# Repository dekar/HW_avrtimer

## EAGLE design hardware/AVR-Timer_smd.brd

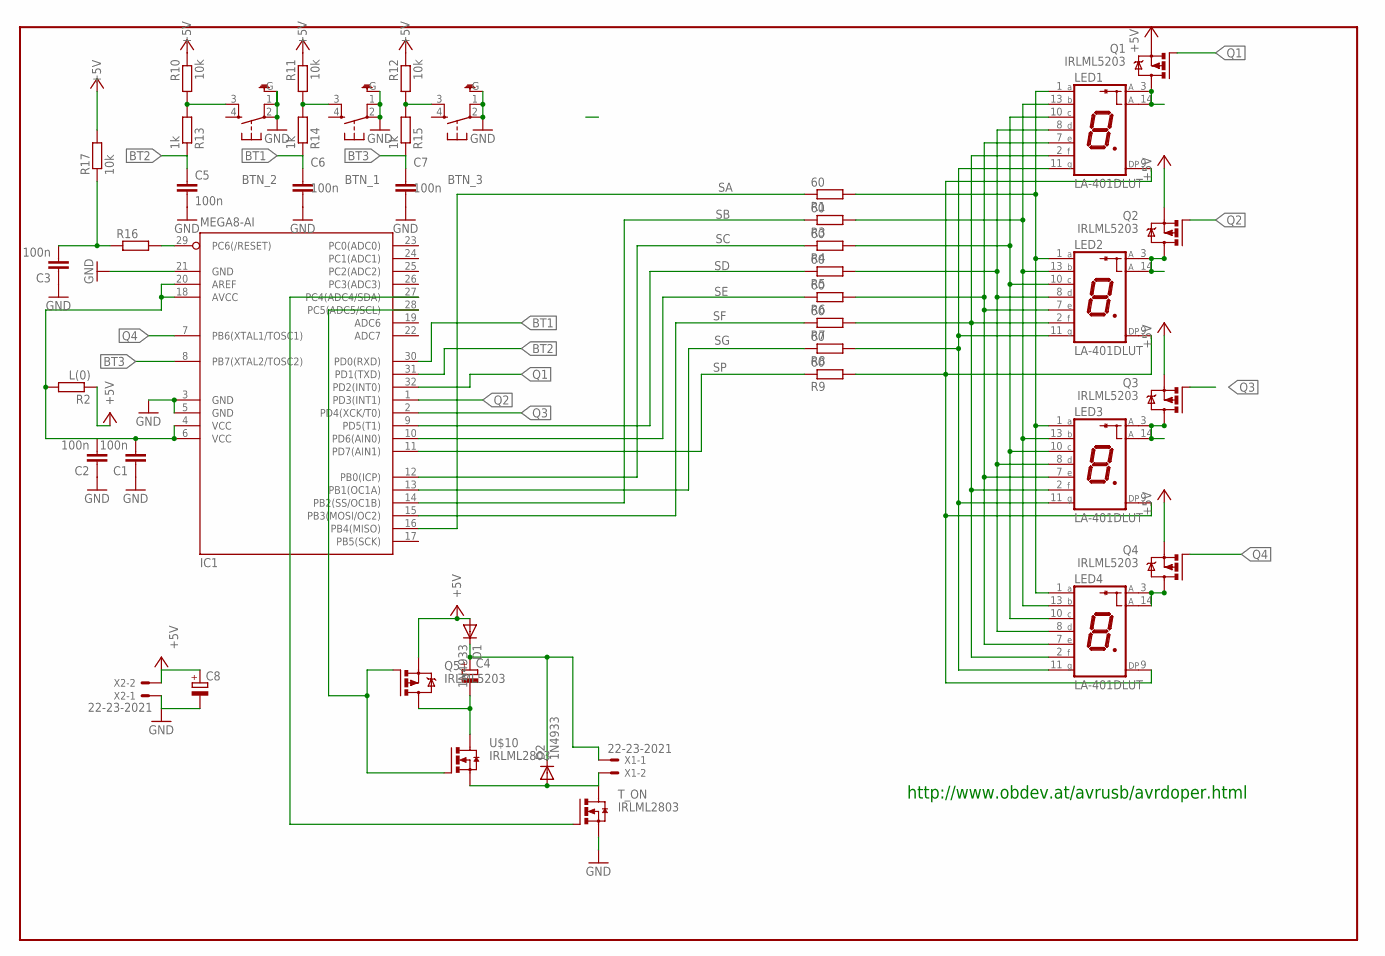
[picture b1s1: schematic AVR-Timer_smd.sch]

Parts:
BTN_1, BTN_2, BTN_3: 10-XXG; B3F-10XXG
C1, C2, C3, C5, C6, C7: 100n; C0805K
C4, C8: CPOL-EUE5-8.5; E5-8,5
D1, D2: 1N4933; DO41-10
IC1: MEGA8-AI; TQFP32-08
LED1, LED2, LED3, LED4: LA-401DLUT; MY_LUT
Q1, Q2, Q3, Q4, Q5: IRLML5203; MICRO3
R1, R3, R4, R5, R6, R7, R8, R9: 60; M0805
R2: L(0); M1206
R10, R11, R12: 10k; M0805
R13, R14, R15: 1k; M0805
R16: R-EU_M1206; M1206
R17: 10k; M1206
T_ON: IRLML2803; SUPER-SOT3
U$10: IRLML2803; SUPER-SOT3
X1: 22-23-2021
X2: 22-23-2021; MPN 22-23-2021

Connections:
+5V: C8.+, D1.A, Q1.2 (S), Q2.2 (S), Q3.2 (S), Q4.2 (S), Q5.2 (S), R2.1, R10.1, R11.1, R12.1, R17.2, X2.2
BT1: C6.1, IC1.30 (PD0(RXD)), R14.1
BT2: C5.1, IC1.31 (PD1(TXD)), R13.1
BT3: C7.1, IC1.8 (PB7(XTAL2/TOSC2)), R15.1
GND: BTN_1.1, BTN_1.2, BTN_1.G (GND), BTN_2.1, BTN_2.2, BTN_2.G (GND), BTN_3.1, BTN_3.2, BTN_3.G (GND), C1.1, C2.1, C3.1, C5.2, C6.2, C7.2, C8.-, IC1.3 (GND), IC1.5 (GND), IC1.21 (GND), T_ON.2 (S), X2.1
unnamed: C1.2, C2.2, IC1.4 (VCC), IC1.6 (VCC), IC1.18 (AVCC), IC1.20 (AREF), R2.2
unnamed: BTN_2.3 (S1), R10.2, R13.2
unnamed: BTN_1.3 (S1), R11.2, R14.2
unnamed: BTN_3.3 (S1), R12.2, R15.2
unnamed: C3.2, R16.1, R17.1
unnamed: LED1.1 (A), LED2.1 (A), LED3.1 (A), LED4.1 (A), R1.2
unnamed: LED1.13 (B), LED2.13 (B), LED3.13 (B), LED4.13 (B), R3.2
unnamed: LED1.10 (C), LED2.10 (C), LED3.10 (C), LED4.10 (C), R4.2
unnamed: LED1.8 (D), LED2.8 (D), LED3.8 (D), LED4.8 (D), R5.2
unnamed: LED1.7 (E), LED2.7 (E), LED3.7 (E), LED4.7 (E), R6.2
unnamed: LED1.9 (DP), LED2.9 (DP), LED3.9 (DP), LED4.9 (DP), R9.2
unnamed: LED1.11 (G), LED2.11 (G), LED3.11 (G), LED4.11 (G), R8.2
unnamed: LED3.3 (A), LED3.14 (A), Q3.3 (D)
unnamed: LED2.3 (A), LED2.14 (A), Q2.3 (D)
unnamed: LED4.3 (A), LED4.14 (A), Q4.3 (D)
unnamed: LED1.2 (F), LED2.2 (F), LED3.2 (F), LED4.2 (F), R7.2
unnamed: LED1.3 (A), LED1.14 (A), Q1.3 (D)
unnamed: C4.-, Q5.3 (D), U$10.3 (D)
unnamed: IC1.28 (PC5(ADC5/SCL)), Q5.1 (G), U$10.1 (G)
unnamed: D2.A, T_ON.3 (D), U$10.2 (S), X1.2
unnamed: C4.+, D1.C, D2.C, X1.1
unnamed: IC1.27 (PC4(ADC4/SDA)), T_ON.1 (G)
Q1: IC1.32 (PD2(INT0)), Q1.1 (G)
Q2: IC1.1 (PD3(INT1)), Q2.1 (G)
Q3: IC1.2 (PD4(XCK/T0)), Q3.1 (G)
Q4: IC1.7 (PB6(XTAL1/TOSC1)), Q4.1 (G)
RESET: IC1.29 (PC6(/RESET)), R16.2
SA: IC1.16 (PB4(MISO)), R1.1
SB: IC1.14 (PB2(SS/OC1B)), R3.1
SC: IC1.12 (PB0(ICP)), R4.1
SD: IC1.9 (PD5(T1)), R5.1
SE: IC1.10 (PD6(AIN0)), R6.1
SF: IC1.15 (PB3(MOSI/OC2)), R7.1
SG: IC1.13 (PB1(OC1A)), R8.1
SP: IC1.11 (PD7(AIN1)), R9.1

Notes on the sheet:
http://www.obdev.at/avrusb/avrdoper.html

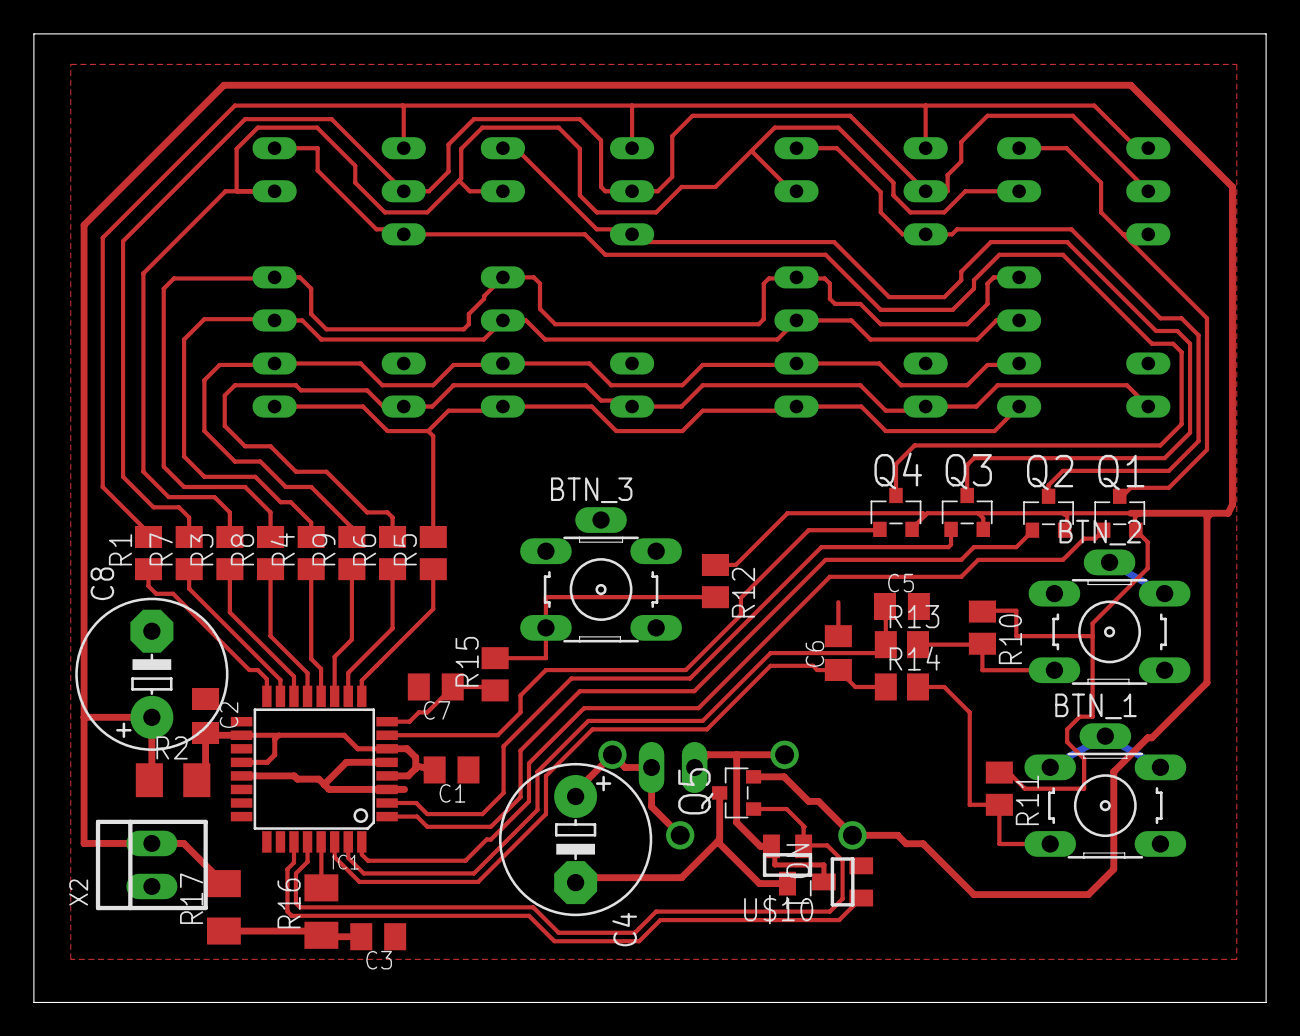
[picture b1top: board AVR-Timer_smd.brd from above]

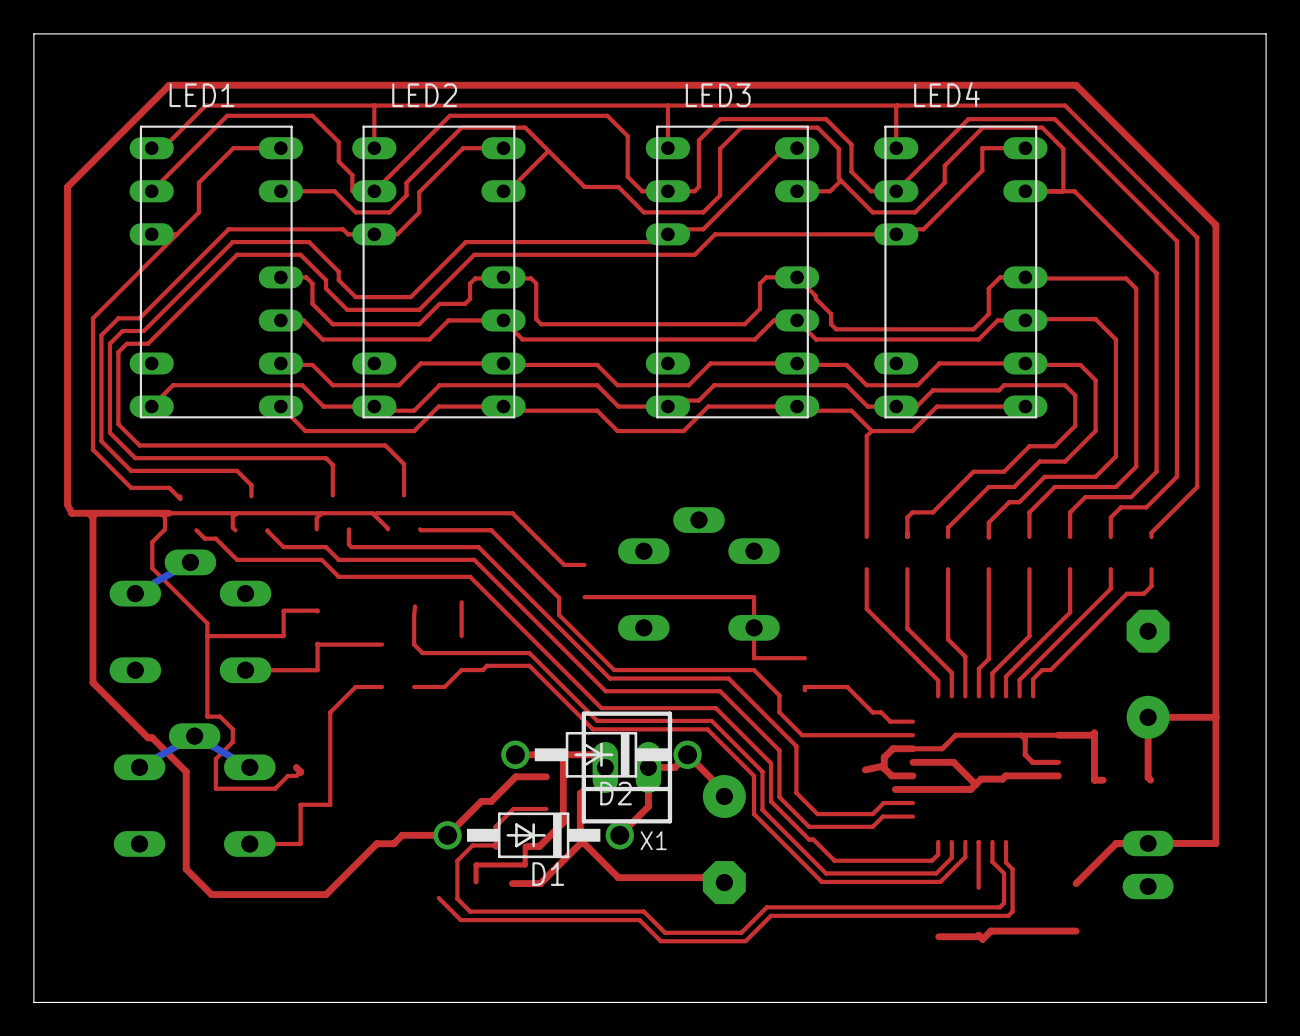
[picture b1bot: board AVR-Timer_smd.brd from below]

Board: 2 copper layers, 72.7 x 57.1 mm, 44 parts (7 on the bottom side), 40 nets.

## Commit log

2017-06-18 add Makefile and some notes to eagle files
